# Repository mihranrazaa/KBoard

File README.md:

# KBoard

## Overview
a 75%% keyboard design, it is based on RP2040 plus with a type C port which came in-built with the MCU, there total of 87 MX switches with 5 Stabilizers. A complete keyboard :).

## Bit in depth info
The keyboard is designed to be sleek and plane it has RP2040 plus as the MCU and Cherry MX Brown Switches for the keys which are used for versatile purposes (that's what i saw at least). The main firmware is KMK based and the Firmware has already been released, you can find that in the Firmware and Production folder, I hate using different cables so having type c inbuilt in the RP2040 plus is a win-win.

---

## Files to build 

### PCB 

The files for the PCB and Schematics are available in the Kicad folder and gerber files are added in the Production folder..

## Images

### Case 

The files for the case and plate are available in the CAD folder and in the Production folder..

---

---

## BOM

| Component                 | Quantity | Note                                                                                    | Price    | Link                                                                                                                                       |
| ------------------------- | -------- | --------------------------------------------------------------------------------------- | -------- | ------------------------------------------------------------------------------------------------------------------------------------------ |
| Akko Yello creamy | 2       | Found a good website!! | 25USD    | [Available](https://stackskb.com/store/akko-v5-creamy-yellow-pro-switch-pack-of-45/)                                                    |
| Grey Keycaps set         | 1        | Good Asthetics are important I will keep the body grey :)                               | 16USD    | [Available](https://stackskb.com/store/white-grey-and-yellow-double-shot-abs-cherry-profile-keycaps/) |
| Stabilizer set            | 1        | PCB Mounted Stabs| 17USD    | [Available](https://stackskb.com/store/durock-smokey-screw-in-stabilizers-v2/)                                                         |
| Case & PCB                | 1        | This is the cheapest i could find                                             | 63USD | https://robu.in/                                                                                                                                         |
| TOTAL                     |          |                                                                                         | 110-120 |                                                                                                                                            |

---

made with <3 by [mihranrazaa](https://mihranrazaa.info/)

BYEEE

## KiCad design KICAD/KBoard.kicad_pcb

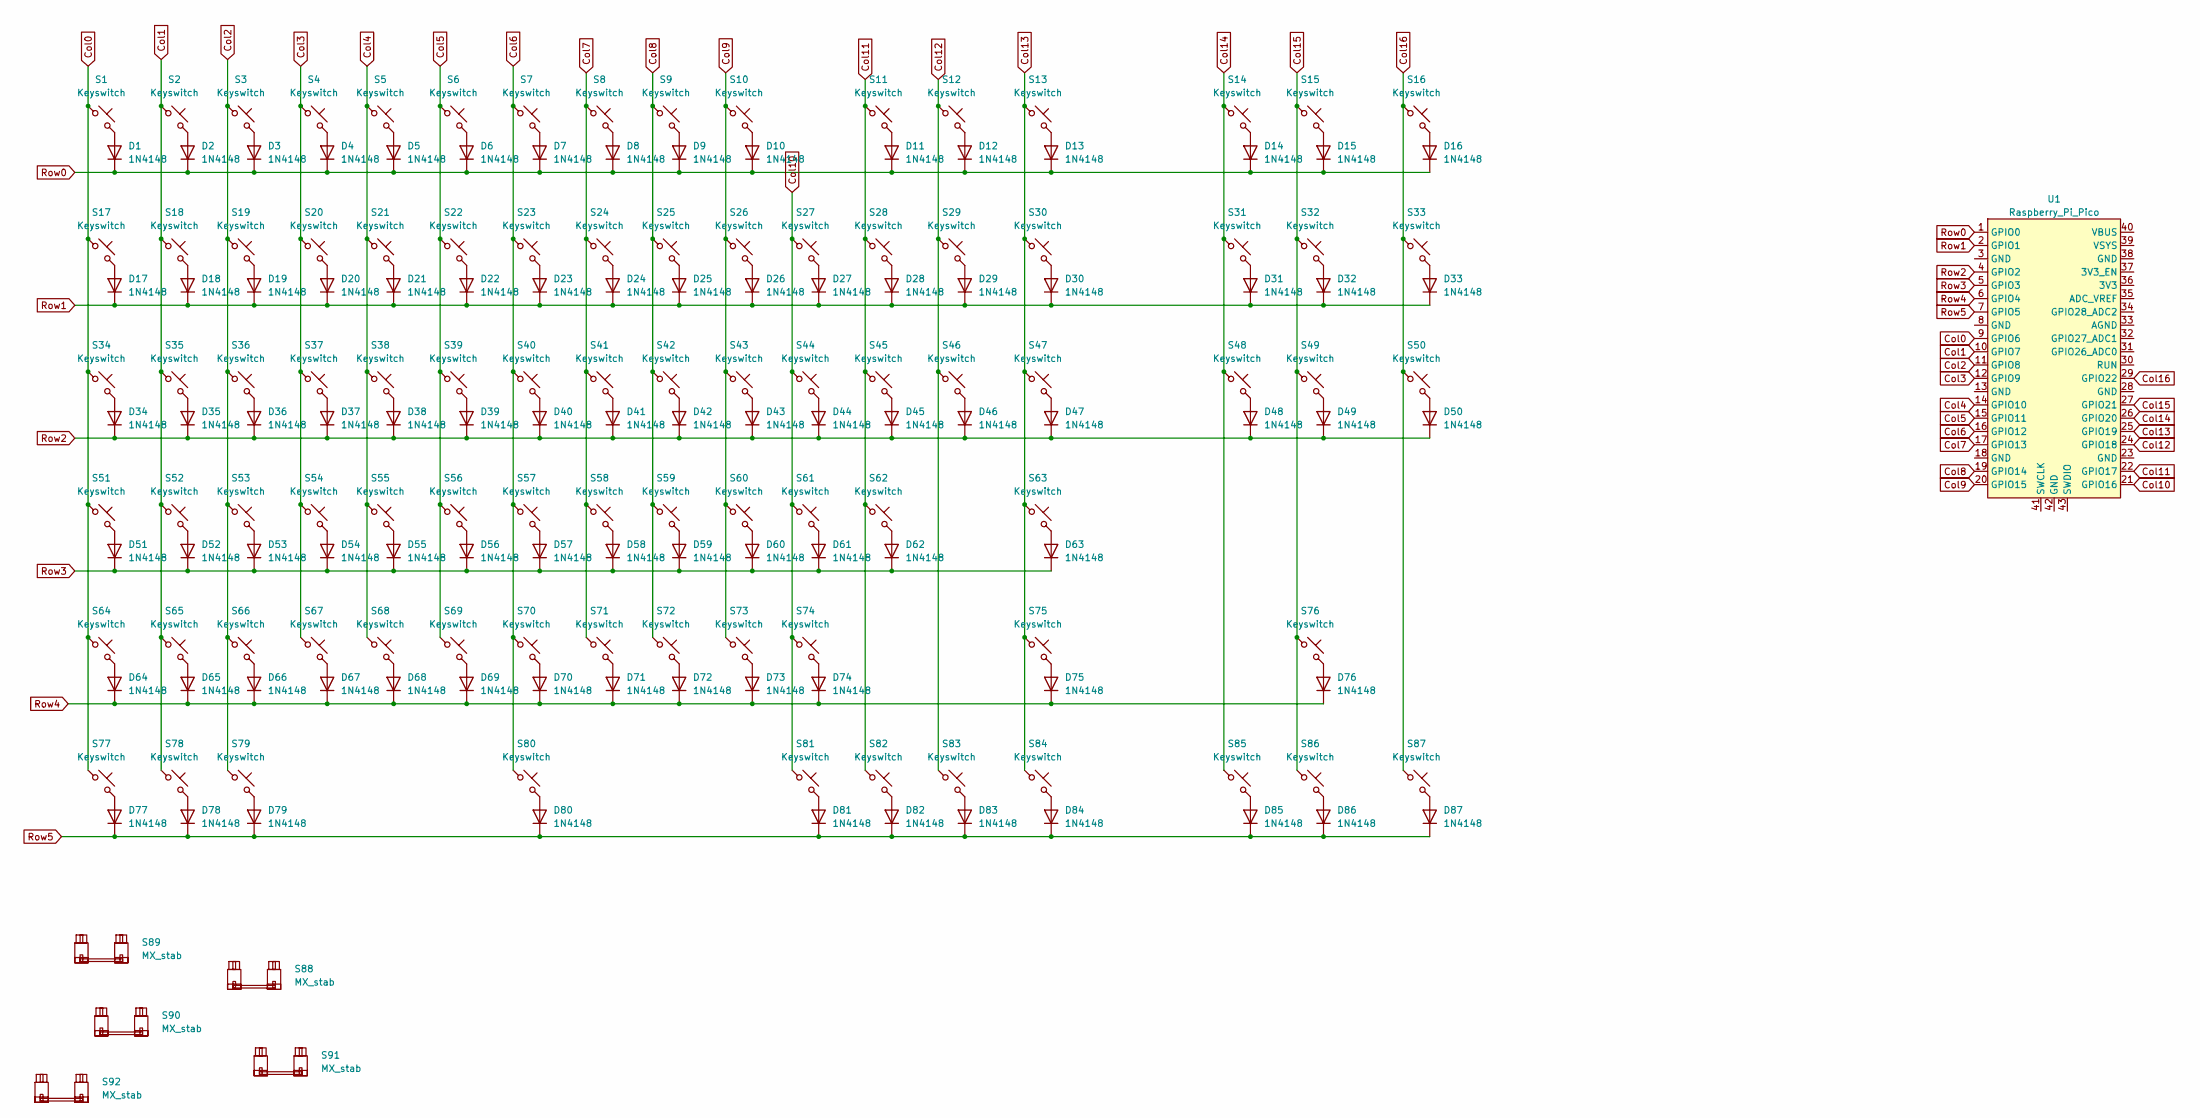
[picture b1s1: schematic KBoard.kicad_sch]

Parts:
D1, D2, D3, D4, D5, D6, D7, D8, D9, D10, D11, D12, D13, D14, D15, D16, D17, D18, D19, D20, D21, D22, D23, D24, D25, D26, D27, D28, D29, D30, D31, D32, D33, D34, D35, D36, D37, D38, D39, D40, D41, D42, D43, D44, D45, D46, D47, D48, D49, D50, D51, D52, D53, D54, D55, D56, D57, D58, D59, D60, D61, D62, D63, D64, D65, D66, D67, D68, D69, D70, D71, D72, D73, D74, D75, D76, D77, D78, D79, D80, D81, D82, D83, D84, D85, D86, D87: 1N4148; D_DO-35_SOD27_P7.62mm_Horizontal
S1, S2, S3, S4, S5, S6, S7, S8, S9, S10, S11, S12, S13, S14, S15, S16, S17, S18, S19, S20, S21, S22, S23, S24, S25, S26, S27, S28, S29, S31, S32, S33, S35, S36, S37, S38, S39, S40, S41, S42, S43, S44, S45, S46, S48, S49, S50, S52, S53, S54, S55, S56, S57, S58, S59, S60, S61, S62, S65, S66, S67, S68, S69, S70, S71, S72, S73, S74, S76, S85, S86, S87: Keyswitch; MX_PCB_1.00u
S30: Keyswitch; MX_PCB_2.00u
S34, S47: Keyswitch; MX_PCB_1.50u
S51: Keyswitch; MX_PCB_1.75u
S63, S64: Keyswitch; MX_PCB_2.25u
S75: Keyswitch; MX_PCB_2.75u
S77, S78, S79, S81, S82, S83, S84: Keyswitch; MX_PCB_1.25u
S80: Keyswitch; MX_PCB_6.25u
S88: MX_stab; STAB_MX_P_6.25u
S89, S90, S91, S92: MX_stab; STAB_MX_P_2u
U1: Raspberry_Pi_Pico

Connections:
Col0: S1.1, S17.1, S34.1, S51.1, S64.1, S77.1, U1.9 (GPIO6)
Col1: S2.1, S18.1, S35.1, S52.1, S65.1, S78.1, U1.10 (GPIO7)
Col2: S3.1, S19.1, S36.1, S53.1, S66.1, S79.1, U1.11 (GPIO8)
Col3: S4.1, S20.1, S37.1, S54.1, S67.1, U1.12 (GPIO9)
Col4: S5.1, S21.1, S38.1, S55.1, S68.1, U1.14 (GPIO10)
Col5: S6.1, S22.1, S39.1, S56.1, S69.1, U1.15 (GPIO11)
Col6: S7.1, S23.1, S40.1, S57.1, S70.1, S80.1, U1.16 (GPIO12)
Col7: S8.1, S24.1, S41.1, S58.1, S71.1, U1.17 (GPIO13)
Col8: S9.1, S25.1, S42.1, S59.1, S72.1, U1.19 (GPIO14)
Col9: S10.1, S26.1, S43.1, S60.1, S73.1, U1.20 (GPIO15)
Col10: S27.1, S44.1, S61.1, S74.1, S81.1, U1.21 (GPIO16)
Col11: S11.1, S28.1, S45.1, S62.1, S82.1, U1.22 (GPIO17)
Col12: S12.1, S29.1, S46.1, S83.1, U1.24 (GPIO18)
Col13: S13.1, S30.1, S47.1, S63.1, S75.1, S84.1, U1.25 (GPIO19)
Col14: S14.1, S31.1, S48.1, S85.1, U1.26 (GPIO20)
Col15: S15.1, S32.1, S49.1, S76.1, S86.1, U1.27 (GPIO21)
Col16: S16.1, S33.1, S50.1, S87.1, U1.29 (GPIO22)
unnamed: D1.2 (A), S1.2
unnamed: D2.2 (A), S2.2
unnamed: D3.2 (A), S3.2
unnamed: D4.2 (A), S4.2
unnamed: D5.2 (A), S5.2
unnamed: D6.2 (A), S6.2
unnamed: D7.2 (A), S7.2
unnamed: D8.2 (A), S8.2
unnamed: D9.2 (A), S9.2
unnamed: D10.2 (A), S10.2
unnamed: D11.2 (A), S11.2
unnamed: D12.2 (A), S12.2
unnamed: D13.2 (A), S13.2
unnamed: D14.2 (A), S14.2
unnamed: D15.2 (A), S15.2
unnamed: D16.2 (A), S16.2
unnamed: D17.2 (A), S17.2
unnamed: D18.2 (A), S18.2
unnamed: D19.2 (A), S19.2
unnamed: D20.2 (A), S20.2
unnamed: D21.2 (A), S21.2
unnamed: D22.2 (A), S22.2
unnamed: D23.2 (A), S23.2
unnamed: D24.2 (A), S24.2
unnamed: D25.2 (A), S25.2
unnamed: D26.2 (A), S26.2
unnamed: D27.2 (A), S27.2
unnamed: D28.2 (A), S28.2
unnamed: D29.2 (A), S29.2
unnamed: D30.2 (A), S30.2
unnamed: D31.2 (A), S31.2
unnamed: D32.2 (A), S32.2
unnamed: D33.2 (A), S33.2
unnamed: D34.2 (A), S34.2
unnamed: D35.2 (A), S35.2
unnamed: D36.2 (A), S36.2
unnamed: D37.2 (A), S37.2
unnamed: D38.2 (A), S38.2
unnamed: D39.2 (A), S39.2
unnamed: D40.2 (A), S40.2
unnamed: D41.2 (A), S41.2
unnamed: D42.2 (A), S42.2
unnamed: D43.2 (A), S43.2
unnamed: D44.2 (A), S44.2
unnamed: D45.2 (A), S45.2
unnamed: D46.2 (A), S46.2
unnamed: D47.2 (A), S47.2
unnamed: D48.2 (A), S48.2
unnamed: D49.2 (A), S49.2
unnamed: D50.2 (A), S50.2
unnamed: D51.2 (A), S51.2
unnamed: D52.2 (A), S52.2
unnamed: D53.2 (A), S53.2
unnamed: D54.2 (A), S54.2
unnamed: D55.2 (A), S55.2
unnamed: D56.2 (A), S56.2
unnamed: D57.2 (A), S57.2
unnamed: D58.2 (A), S58.2
unnamed: D59.2 (A), S59.2
unnamed: D60.2 (A), S60.2
unnamed: D61.2 (A), S61.2
unnamed: D62.2 (A), S62.2
unnamed: D63.2 (A), S63.2
unnamed: D64.2 (A), S64.2
unnamed: D65.2 (A), S65.2
unnamed: D66.2 (A), S66.2
unnamed: D67.2 (A), S67.2
unnamed: D68.2 (A), S68.2
unnamed: D69.2 (A), S69.2
unnamed: D70.2 (A), S70.2
unnamed: D71.2 (A), S71.2
unnamed: D72.2 (A), S72.2
unnamed: D73.2 (A), S73.2
unnamed: D74.2 (A), S74.2
unnamed: D75.2 (A), S75.2
unnamed: D76.2 (A), S76.2
unnamed: D77.2 (A), S77.2
unnamed: D78.2 (A), S78.2
unnamed: D79.2 (A), S79.2
unnamed: D80.2 (A), S80.2
unnamed: D81.2 (A), S81.2
unnamed: D82.2 (A), S82.2
unnamed: D83.2 (A), S83.2
unnamed: D84.2 (A), S84.2
unnamed: D85.2 (A), S85.2
unnamed: D86.2 (A), S86.2
unnamed: D87.2 (A), S87.2
Row0: D1.1 (K), D2.1 (K), D3.1 (K), D4.1 (K), D5.1 (K), D6.1 (K), D7.1 (K), D8.1 (K), D9.1 (K), D10.1 (K), D11.1 (K), D12.1 (K), D13.1 (K), D14.1 (K), D15.1 (K), D16.1 (K), U1.1 (GPIO0)
Row1: D17.1 (K), D18.1 (K), D19.1 (K), D20.1 (K), D21.1 (K), D22.1 (K), D23.1 (K), D24.1 (K), D25.1 (K), D26.1 (K), D27.1 (K), D28.1 (K), D29.1 (K), D30.1 (K), D31.1 (K), D32.1 (K), D33.1 (K), U1.2 (GPIO1)
Row2: D34.1 (K), D35.1 (K), D36.1 (K), D37.1 (K), D38.1 (K), D39.1 (K), D40.1 (K), D41.1 (K), D42.1 (K), D43.1 (K), D44.1 (K), D45.1 (K), D46.1 (K), D47.1 (K), D48.1 (K), D49.1 (K), D50.1 (K), U1.4 (GPIO2)
Row3: D51.1 (K), D52.1 (K), D53.1 (K), D54.1 (K), D55.1 (K), D56.1 (K), D57.1 (K), D58.1 (K), D59.1 (K), D60.1 (K), D61.1 (K), D62.1 (K), D63.1 (K), U1.5 (GPIO3)
Row4: D64.1 (K), D65.1 (K), D66.1 (K), D67.1 (K), D68.1 (K), D69.1 (K), D70.1 (K), D71.1 (K), D72.1 (K), D73.1 (K), D74.1 (K), D75.1 (K), D76.1 (K), U1.6 (GPIO4)
Row5: D77.1 (K), D78.1 (K), D79.1 (K), D80.1 (K), D81.1 (K), D82.1 (K), D83.1 (K), D84.1 (K), D85.1 (K), D86.1 (K), D87.1 (K), U1.7 (GPIO5)

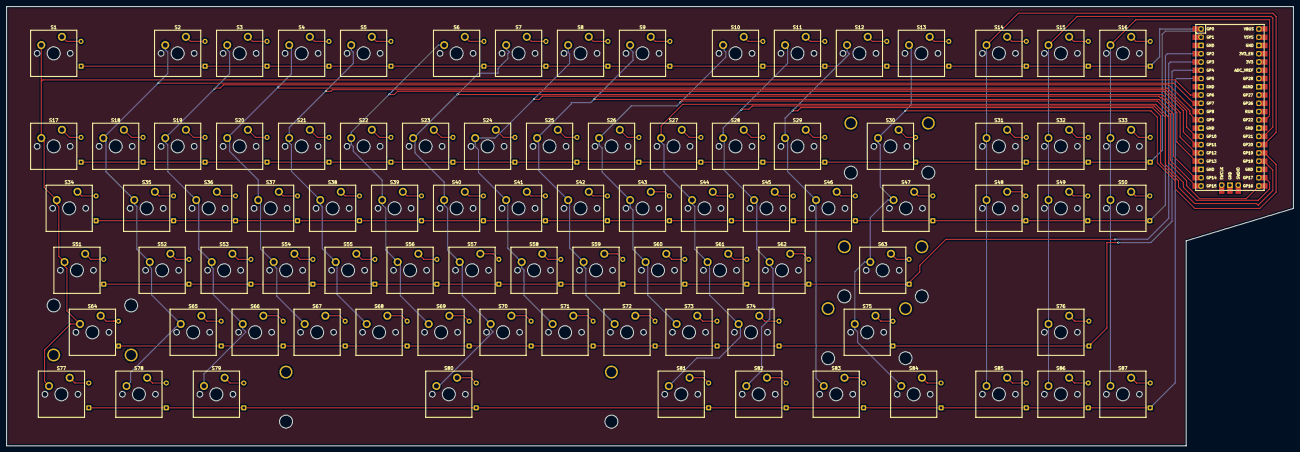
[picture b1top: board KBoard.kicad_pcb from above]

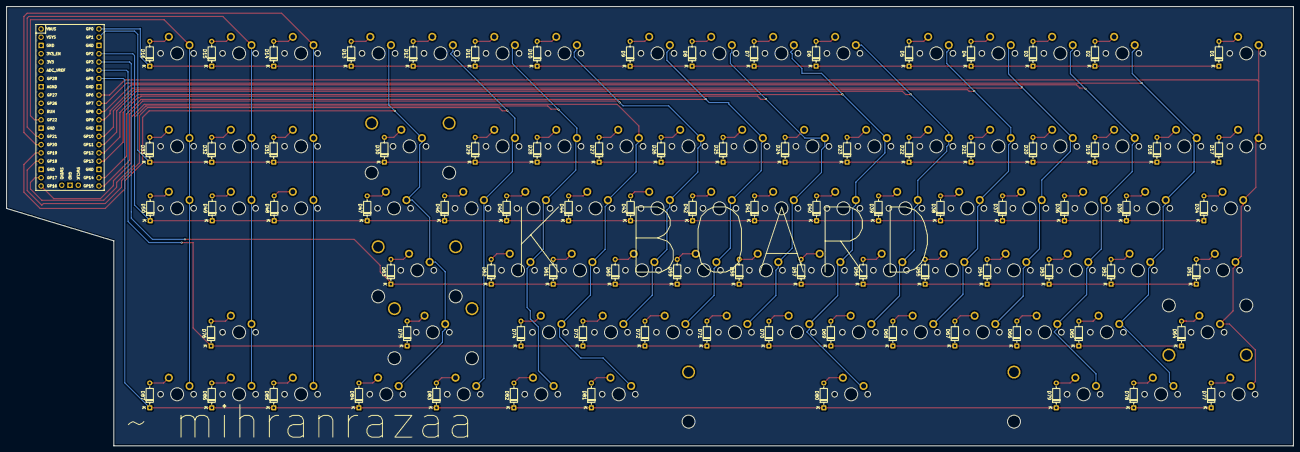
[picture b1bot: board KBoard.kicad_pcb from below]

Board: 2 copper layers, 395.5 x 135.0 mm, 180 parts (87 on the bottom side), 110 nets.

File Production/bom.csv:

Designator,Footprint,Quantity,Value,LCSC Part #
"D1, D10, D11, D12, D13, D14, D15, D16, D17, D18, D19, D2, D20, D21, D22, D23, D24, D25, D26, D27, D28, D29, D3, D30, D31, D32, D33, D34, D35, D36, D37, D38, D39, D4, D40, D41, D42, D43, D44, D45, D46, D47, D48, D49, D5, D50, D51, D52, D53, D54, D55, D56, D57, D58, D59, D6, D60, D61, D62, D63, D64, D65, D66, D67, D68, D69, D7, D70, D71, D72, D73, D74, D75, D76, D77, D78, D79, D8, D80, D81, D82, D83, D84, D85, D86, D87, D9",D_DO-35_SOD27_P7.62mm_Horizontal,87,1N4148,
"S1, S10, S11, S12, S13, S14, S15, S16, S17, S18, S19, S2, S20, S21, S22, S23, S24, S25, S26, S27, S28, S29, S3, S31, S32, S33, S35, S36, S37, S38, S39, S4, S40, S41, S42, S43, S44, S45, S46, S48, S49, S5, S50, S52, S53, S54, S55, S56, S57, S58, S59, S6, S60, S61, S62, S65, S66, S67, S68, S69, S7, S70, S71, S72, S73, S74, S76, S8, S85, S86, S87, S9",MX_PCB_1.00u,72,Keyswitch,
S30,MX_PCB_2.00u,1,Keyswitch,
"S34, S47",MX_PCB_1.50u,2,Keyswitch,
S51,MX_PCB_1.75u,1,Keyswitch,
"S63, S64",MX_PCB_2.25u,2,Keyswitch,
S75,MX_PCB_2.75u,1,Keyswitch,
"S77, S78, S79, S81, S82, S83, S84",MX_PCB_1.25u,7,Keyswitch,
S80,MX_PCB_6.25u,1,Keyswitch,
S88,STAB_MX_P_6.25u,1,MX_stab,
"S89, S90, S91, S92",STAB_MX_P_2u,4,MX_stab,
U1,Raspberry_Pi_Pico,1,Raspberry_Pi_Pico,

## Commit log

2025-09-27 Initial update
2026-04-09 add case and update readme
2026-04-27 resolve issues
